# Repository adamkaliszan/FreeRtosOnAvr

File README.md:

# FreeRtosOnAvr

An alternative for arduino. Multitasking firmware provides great flexibility.

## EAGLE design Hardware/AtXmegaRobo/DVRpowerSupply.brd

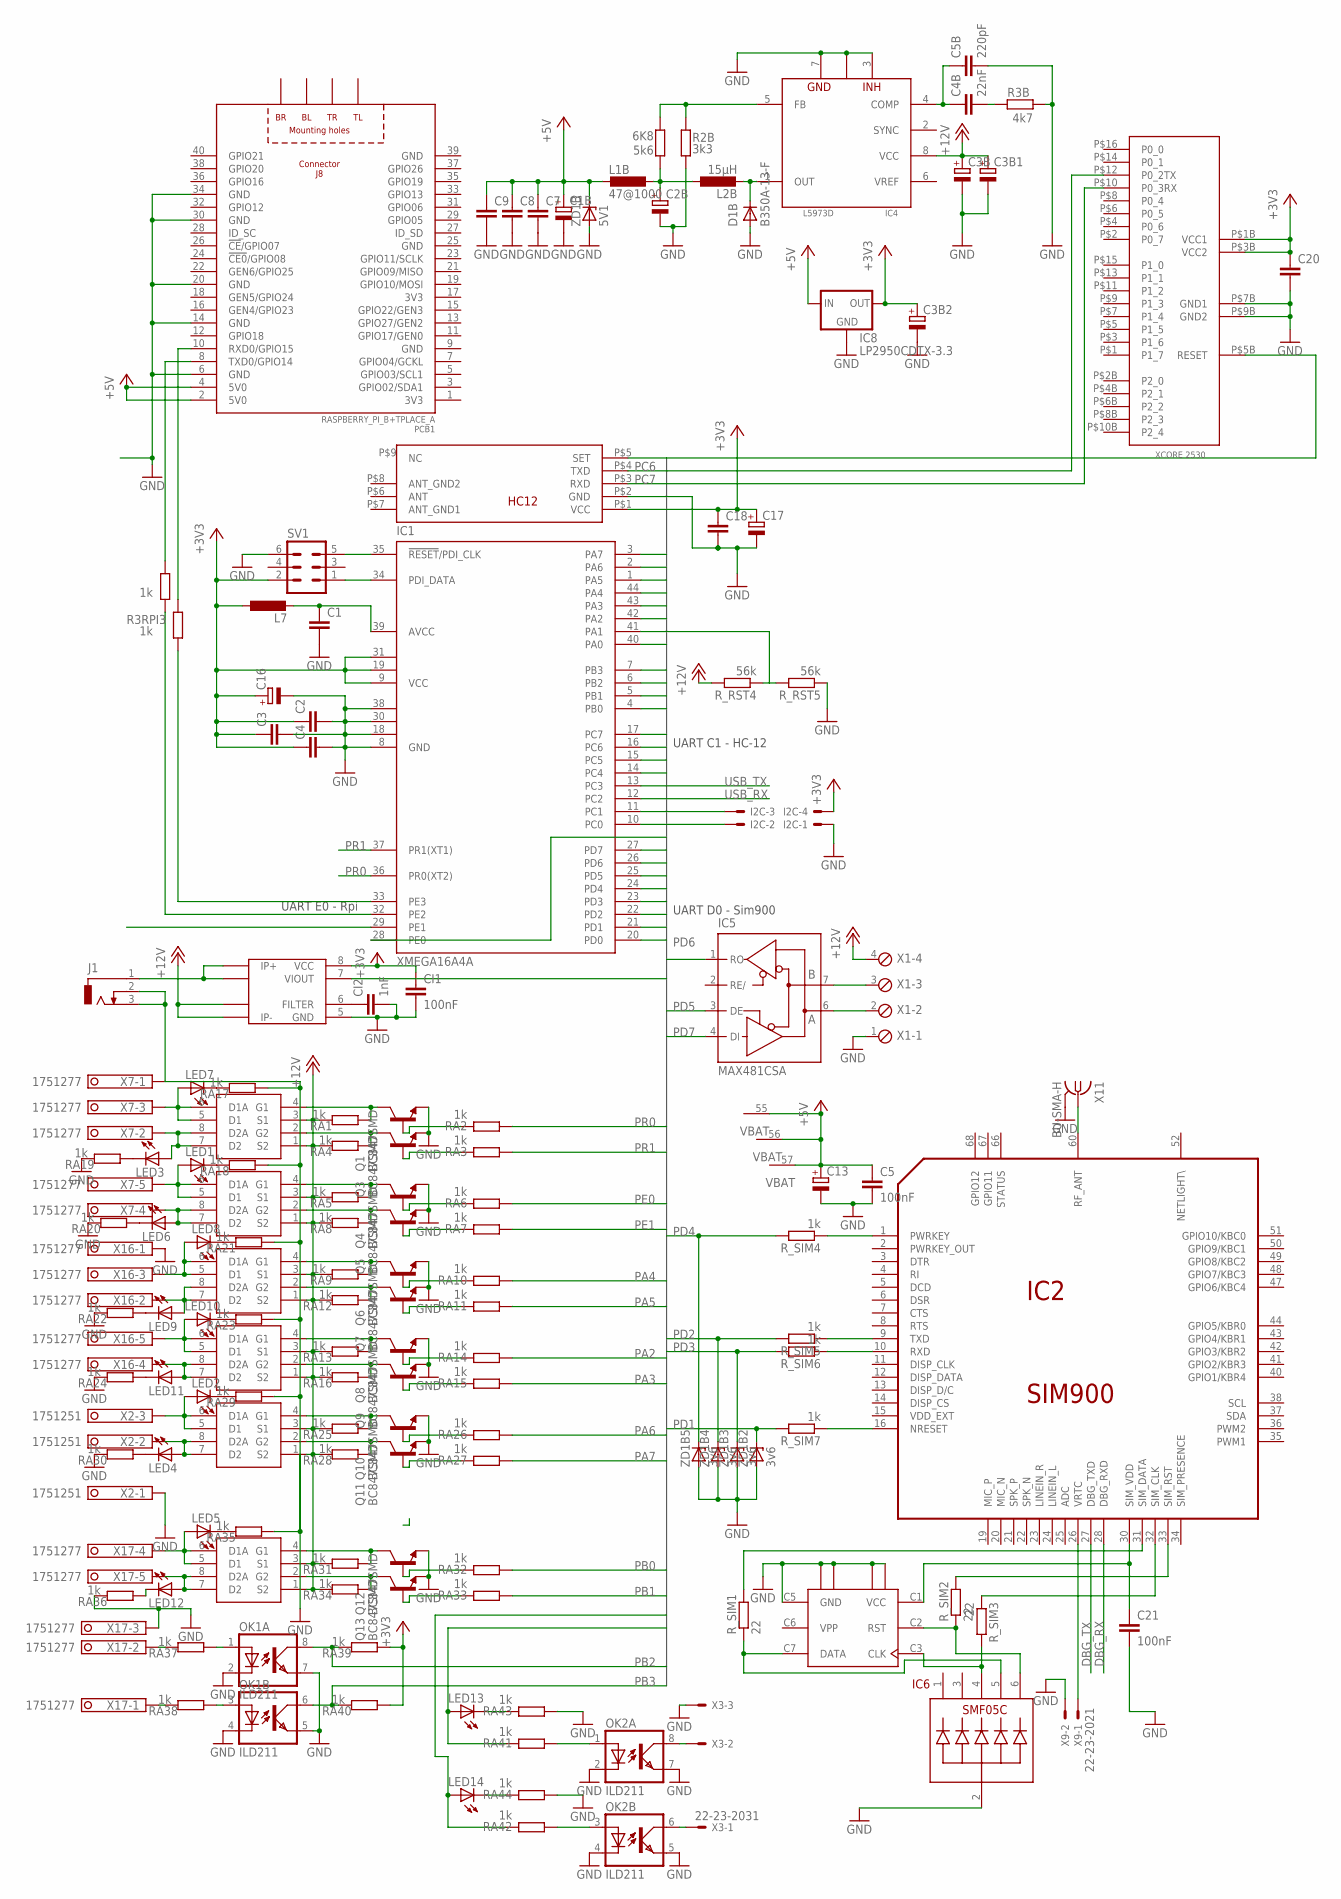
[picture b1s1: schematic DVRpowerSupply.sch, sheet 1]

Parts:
6K8: 5k6; R1206
C1, C2, C3, C4, C18, C20: C-EUC0805; C0805
C1B, C2B, C3B, C16: CPOL-EU153CLV-0405; 153CLV-0405
C3B1, C13: CPOL-EU153CLV-0605; 153CLV-0605
C3B2: CPOL-EU150CLZ-0810; 150CLZ-0810
C4B: 22nF; C0805
C5, C21: 100nF; C1206
C5B: 220pF; C0805
C7, C8, C9: C-EUC1206K; C1206K
C17: CPOL-EU140CLH-0810; 140CLH-0810
CI1: 100nF; C0805
CI2: 1nF; C0805
D1B: B350A-13-F; SMA-DO214AC
I2C: 22-23-2041
IC1: XMEGA16A4A; TQFP44
IC2: SIM900
IC4: L5973D; HSOP8-PAD
IC5: MAX481CSA; SO08
IC6: SMF05C; SC-70-6
IC8: LP2950CDTX-3.3; DPACK
J1: DCJ0303
L1B: 47@1000; L4532P
L2B: 15µH; POWER-CHOKE_WE-TPC
L7: L-EUL4035M; L4035M
LED1, LED2, LED3, LED4, LED5, LED6, LED7, LED8, LED9, LED10, LED11, LED12, LED13, LED14: LEDCHIPLED_0805; CHIPLED_0805
OK1, OK2: ILD211; SOIC08
PCB1: RASPBERRY_PI_B+TPLACE_A; RASPBERRY_PI_APLUS_TPLACE
Q1, Q3, Q4, Q5, Q6, Q7, Q8, Q9, Q10, Q11, Q12, Q13: BC847SMD; SOT23
R2B: 3k3; R1206
R3B: 4k7; R1206
R3RPI2, R3RPI3: 1k; R1206
RA1, RA2, RA3, RA4, RA5, RA6, RA7, RA8, RA9, RA10, RA11, RA12, RA13, RA14, RA15, RA16, RA17, RA18, RA19, RA20, RA21, RA22, RA23, RA24, RA25, RA26, RA27, RA28, RA29, RA30, RA31, RA32, RA33, RA34, RA35, RA36, RA37, RA38, RA39, RA40, RA41, RA42, RA43, RA44: 1k; R0805
R_RST4, R_RST5: 56k; R1206
R_SIM1, R_SIM2, R_SIM3: 22; R1206
R_SIM4, R_SIM5, R_SIM6, R_SIM7: 1k; R1206
SV1: ML6
U$1, U$2, U$9, U$10, U$11, U$12: AO4801A; SO-08
U$3: HC-12
U$4: XCORE2530
U$7: SCU-W0822XR-06115R-BCA0; 115R-BCA0
U$8: ACS712SO8; SO-08M
X1: MPT4; 4POL254
X2: 1751251
X3: 22-23-2031
X7, X16, X17: 1751277
X9: 22-23-2021
X11: BU-SMA-H
ZD1B: 5V1; SOD80C
ZD1B2, ZD1B3, ZD1B4, ZD1B5: 3v6; SOD80C

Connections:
3V3: PCB1.1 (3V3), PCB1.17 (3V3)
+3V3: C2.1, C3.1, C3B2.+, C4.1, C16.+, C17.+, C18.1, C20.1, CI1.1, I2C.4, IC1.9 (VCC), IC1.19 (VCC1), IC1.31 (VCC2), IC5.8 (VCC), IC8.3 (OUT), L7.1, RA39.1, RA40.1, SV1.2, U$3.P$1 (VCC), U$4.P$1B (VCC1), U$4.P$3B (VCC2), U$8.8 (VCC); also elsewhere on the board
+5V: C1B.+, C5.1, C7.1, C8.1, C9.1, C13.+, IC2.55 (VBAT), IC2.56 (VBAT), IC2.57 (VBAT), IC8.1 (IN), L1B.2, PCB1.2 (5V0), PCB1.4 (5V0), ZD1B.C; also elsewhere on the board
+12V: C3B.+, C3B1.+, IC4.8 (VCC), RA1.2, RA4.2, RA5.2, RA8.2, RA9.2, RA12.2, RA13.2, RA16.2, RA25.2, RA28.2, RA31.2, RA34.2, R_RST4.2, U$1.1 (S2), U$1.3 (S1), U$2.1 (S2), U$2.3 (S1), U$8.3 (IP-3), U$8.4 (IP-), U$9.1 (S2), U$9.3 (S1), U$10.1 (S2), U$10.3 (S1), U$11.1 (S2), U$11.3 (S1), U$12.1 (S2), U$12.3 (S1), X1.4
AVCC: C1.1, IC1.39 (AVCC), L7.2
COMP2: C4B.1, C5B.1, IC4.4 (COMP)
CPU_RST: IC1.35 (!RESET!/PDI_CLK), SV1.5
DBG_RX: IC2.28 (DBG_RXD); also elsewhere on the board
DBG_TX: IC2.27 (DBG_TXD); also elsewhere on the board
GND: C1.2, C1B.-, C2.2, C2B.-, C3.2, C3B.-, C3B1.-, C3B2.-, C4.2, C5.2, C5B.2, C7.2, C8.2, C9.2, C13.-, C16.-, C17.-, C18.2, C20.2, C21.2, CI1.2, CI2.2, D1B.A, I2C.1, IC1.8 (GND), IC1.18 (GND1), IC1.30 (GND2), IC1.38 (GND3), IC2.17 (GND), IC2.18 (GND), IC2.29 (GND), IC2.39 (GND), IC2.45 (GND), IC2.46 (GND), IC2.53 (GND), IC2.54 (GND), IC2.58 (GND), IC2.59 (GND), IC2.61 (GND), IC2.62 (GND), IC2.63 (GND), IC2.64 (GND), IC2.65 (GND), IC4.3 (INH), IC4.7 (GND), IC4.P (GND), IC5.5 (GND), IC6.2, IC8.4 (GND), J1.2, J1.3, OK1.2 (C), OK1.4 (C), OK1.5 (EMIT), OK1.7 (EMIT), OK2.2 (C), OK2.4 (C), OK2.5 (EMIT), OK2.7 (EMIT), PCB1.6 (GND), PCB1.9 (GND), PCB1.14 (GND), PCB1.20 (GND), PCB1.25 (GND), PCB1.30 (GND), PCB1.34 (GND), PCB1.39 (GND), Q1.2 (E), Q3.2 (E), Q4.2 (E), Q5.2 (E), Q6.2 (E), Q7.2 (E), Q8.2 (E), Q9.2 (E), Q10.2 (E), Q11.2 (E), Q12.2 (E), Q13.2 (E), R2B.1, R3B.1, RA17.1, RA18.1, RA19.2, RA20.2, RA21.1, RA22.2, RA23.1, RA24.2, RA29.1, RA30.2, RA35.1, RA36.2, RA43.1, RA44.1, R_RST5.1, SV1.6, U$3.P$2 (GND), U$4.P$7B (GND1), U$4.P$9B (GND2), U$7.C5 (GND), U$7.P$1 (GND4), U$7.P$2 (GND3), U$7.P$3 (GND2), U$7.P$4 (GND1), U$8.5 (GND), X1.1, X2.1, X3.3, X7.1, X9.2, X11.2, X11.3 (2), X11.4 (2), X11.5 (2), X16.1, X17.3, ZD1B.A, ZD1B2.A, ZD1B3.A, ZD1B4.A, ZD1B5.A; also elsewhere on the board
IC4_FB: 6K8.1, IC4.5 (FB), R2B.2
unnamed: OK2.6 (COL), X3.1
unnamed: OK2.8 (COL), X3.2
unnamed: PCB1.8 (TXD0/GPIO14), R3RPI2.2
unnamed: LED4.A, U$11.7 (D2), U$11.8 (D2A), X2.2
unnamed: LED7.A, U$1.5 (D1), U$1.6 (D1A), X7.3
unnamed: LED3.A, U$1.7 (D2), U$1.8 (D2A), X7.2
unnamed: LED7.C, RA17.2
unnamed: LED1.A, U$2.5 (D1), U$2.6 (D1A), X7.5
unnamed: LED2.A, U$11.5 (D1), U$11.6 (D1A), X2.3
unnamed: Q10.3 (C), RA25.1, U$11.4 (G1)
unnamed: CI2.1, U$8.6 (FILTER)
unnamed: LED6.A, U$2.7 (D2), U$2.8 (D2A), X7.4
unnamed: LED8.A, U$9.5 (D1), U$9.6 (D1A), X16.3
unnamed: LED9.A, U$9.7 (D2), U$9.8 (D2A), X16.2
unnamed: LED11.A, U$10.7 (D2), U$10.8 (D2A), X16.4
unnamed: D1B.K (C), IC4.1 (OUT), L2B.2
unnamed: 6K8.2, C2B.+, L1B.1, L2B.1
unnamed: LED10.A, U$10.5 (D1), U$10.6 (D1A), X16.5
unnamed: OK2.1 (A), RA41.1
unnamed: Q1.3 (C), RA1.1, U$1.4 (G1)
unnamed: C4B.2, R3B.2
unnamed: IC2.9 (TXD), R_SIM5.1
unnamed: Q4.3 (C), RA5.1, U$2.4 (G1)
unnamed: Q1.1 (B), RA2.2
unnamed: Q3.1 (B), RA3.2
unnamed: IC2.26 (VRTC), X9.1
unnamed: Q3.3 (C), RA4.1, U$1.2 (G2)
unnamed: IC2.10 (RXD), R_SIM6.1
unnamed: OK2.3 (A), RA42.1
unnamed: Q10.1 (B), RA26.2
unnamed: IC2.16 (NRESET), R_SIM7.1
unnamed: PCB1.10 (RXD0/GPIO15), R3RPI3.2
unnamed: IC2.60 (RF_ANT), X11.1
unnamed: Q4.1 (B), RA6.2
unnamed: Q5.1 (B), RA7.2
unnamed: Q5.3 (C), RA8.1, U$2.2 (G2)
unnamed: Q6.3 (C), RA9.1, U$9.4 (G1)
unnamed: Q6.1 (B), RA10.2
unnamed: Q7.1 (B), RA11.2
unnamed: Q7.3 (C), RA12.1, U$9.2 (G2)
unnamed: Q8.3 (C), RA13.1, U$10.4 (G1)
unnamed: Q8.1 (B), RA14.2
unnamed: Q9.1 (B), RA15.2
unnamed: Q9.3 (C), RA16.1, U$10.2 (G2)
unnamed: LED1.C, RA18.2
unnamed: LED3.C, RA19.1
unnamed: LED6.C, RA20.1
unnamed: LED8.C, RA21.2
unnamed: LED9.C, RA22.1
unnamed: LED10.C, RA23.2
unnamed: LED11.C, RA24.1
unnamed: Q11.1 (B), RA27.2
unnamed: Q11.3 (C), RA28.1, U$11.2 (G2)
unnamed: LED2.C, RA29.2
unnamed: LED4.C, RA30.1
unnamed: LED12.A, U$12.7 (D2), U$12.8 (D2A), X17.5
unnamed: LED5.A, U$12.5 (D1), U$12.6 (D1A), X17.4
unnamed: Q12.3 (C), RA31.1, U$12.4 (G1)
unnamed: Q12.1 (B), RA32.2
unnamed: Q13.1 (B), RA33.2
unnamed: Q13.3 (C), RA34.1, U$12.2 (G2)
unnamed: LED5.C, RA35.2
unnamed: LED12.C, RA36.1
unnamed: RA37.2, X17.2
unnamed: OK1.1 (A), RA37.1
unnamed: RA38.2, X17.1
unnamed: OK1.3 (A), RA38.1
unnamed: LED13.C, RA43.2
unnamed: LED14.C, RA44.2
PA0: IC1.40 (PA0), U$8.7 (VIOUT)
PA1: IC1.41 (PA1), R_RST4.1, R_RST5.2
PA2: IC1.42 (PA2), RA14.1
PA3: IC1.43 (PA3), RA15.1
PA4: IC1.44 (PA4), RA10.1
PA5: IC1.1 (PA5), RA11.1
PA6: IC1.2 (PA6), RA26.1
PA7: IC1.3 (PA7), RA27.1
PB0: IC1.4 (PB0), RA32.1
PB1: IC1.5 (PB1), RA33.1
PB2: IC1.6 (PB2), OK1.8 (COL), RA39.2
PB3: IC1.7 (PB3), OK1.6 (COL), RA40.2
PC0: I2C.2, IC1.10 (PC0)
PC1: I2C.3, IC1.11 (PC1)
PC4: IC1.14 (PC4), LED14.A, RA42.2
PC5: IC1.15 (PC5), LED13.A, RA41.2
PC6: IC1.16 (PC6), U$3.P$4 (TXD), U$4.P$12 (P0_2TX)
PC7: IC1.17 (PC7), U$3.P$3 (RXD), U$4.P$10 (P0_3RX)
PD0: IC1.20 (PD0), U$3.P$5 (SET), U$4.P$5B (RESET)
PD1: IC1.21 (PD1), R_SIM7.2, ZD1B2.C
PD2: IC1.22 (PD2), R_SIM5.2, ZD1B4.C
PD3: IC1.23 (PD3), R_SIM6.2, ZD1B3.C
PD4: IC1.24 (PD4), R_SIM4.2, ZD1B5.C
PD5: IC1.25 (PD5), IC5.3 (DE)
PD6: IC1.26 (PD6), IC5.1 (RO)
PD7: IC1.27 (PD7), IC5.4 (DI)
PDI_DTA: IC1.34 (PDI_DATA), SV1.1
PE0: IC1.28 (PE0), RA6.1
PE1: IC1.29 (PE1), RA7.1
PE2: IC1.32 (PE2), R3RPI2.1
PE3: IC1.33 (PE3), R3RPI3.1
PR0: IC1.36 (PR0(XT2)), RA2.1
PR1: IC1.37 (PR1(XT1)), RA3.1
PWR: J1.1, U$8.1 (IP+), U$8.2 (IP+2)
RS_485_A: IC5.6 (A), X1.2
RS_485_B: IC5.7 (B), X1.3
SIM900PWRKEY: IC2.1 (PWRKEY), R_SIM4.1
SIMCLS_S: IC6.4, R_SIM3.2, U$7.C3 (CLK)
SIMRSTS: IC6.6, R_SIM2.1, U$7.C2 (RST)
SIM_CLK: IC2.32 (SIM_CLK), R_SIM3.1
SIM_DTA: IC2.31 (SIM_DATA), R_SIM1.2
SIM_DTA_S: IC6.5, R_SIM1.1, U$7.C7 (DATA)
SIM_RST: IC2.33 (SIM_RST), R_SIM2.2
SIM_VCC: C21.1, IC2.30 (SIM_VDD), U$7.C1 (VCC)
USB_RX: IC1.12 (PC2); also elsewhere on the board
USB_TX: IC1.13 (PC3); also elsewhere on the board
VPP: U$7.C6 (VPP)

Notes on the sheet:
UART C1 - HC-12
UART D0 - Sim900
UART E0 - Rpi

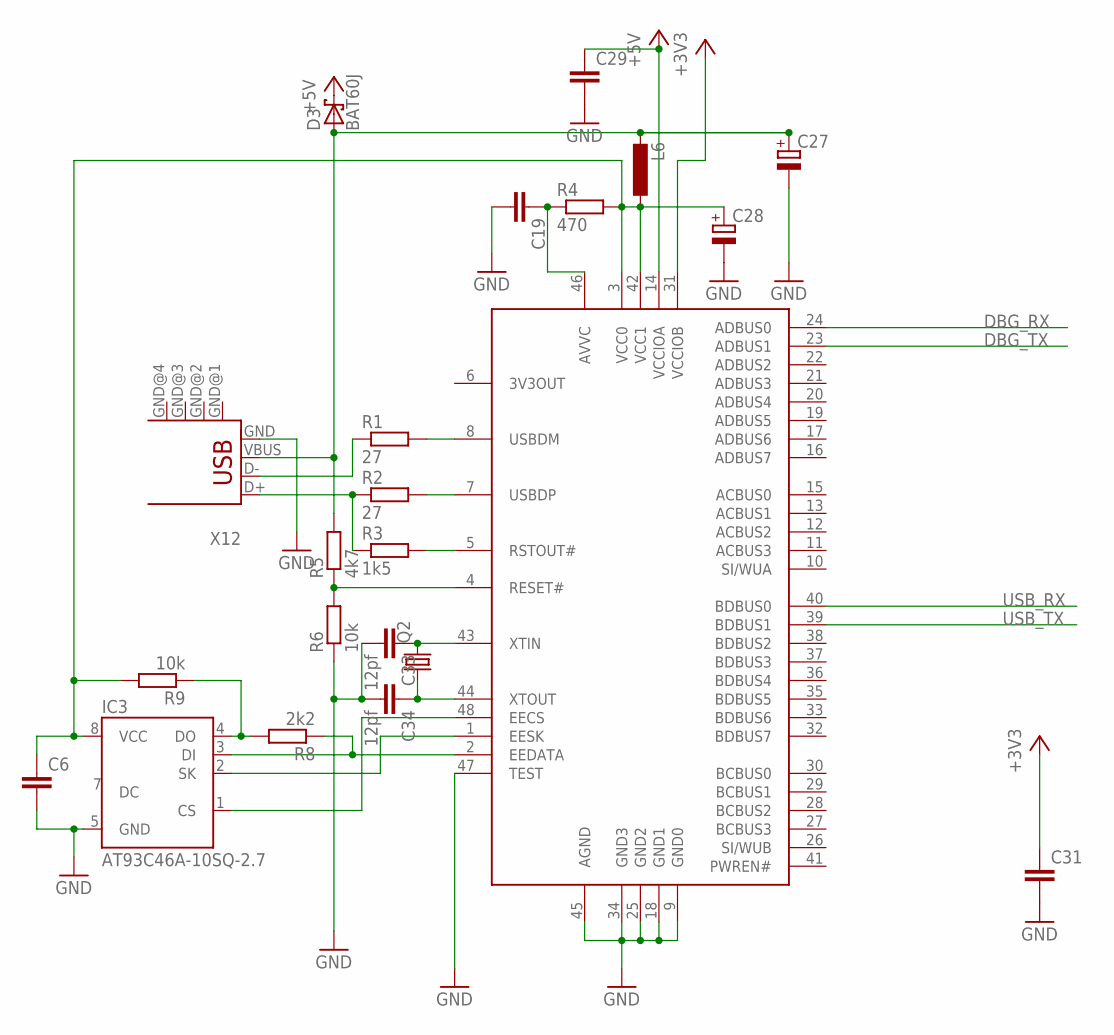
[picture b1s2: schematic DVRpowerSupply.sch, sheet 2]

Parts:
C6: C-EUC0805K; C0805K
C19: C-EUC0805; C0805
C27, C28: CPOL-EU153CLV-0405; 153CLV-0405
C29, C31: C-EUC1206; C1206
C33, C34: 12pf; C0805
D3: BAT60J; SOD323_ST
IC3: AT93C46A-10SQ-2.7; SOIC8
IC7: FT2232C; LQFP
L6: L-EUL2012C; L2012C
Q2: CRYSTALHC49S; HC49/S
R1, R2: 27; M1206
R3: 1k5; M1206
R4: 470; M0805
R5: 4k7; M1206
R6, R9: 10k; M1206
R8: 2k2; M1206
X12: USB-SHIELD; USB-M-S1

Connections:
+3V3: C31.1, IC7.31 (VCCIOB); also elsewhere on the board
+5V: C29.1, D3.C, IC7.14 (VCCIOA); also elsewhere on the board
DBG_RX: IC7.24 (ADBUS0); also elsewhere on the board
DBG_TX: IC7.23 (ADBUS1); also elsewhere on the board
FD_DI: IC3.3 (DI), IC7.2 (EEDATA), R8.1
FT_AVCC: C19.1, IC7.46 (AVVC), R4.1
FT_CS: IC3.1 (CS), IC7.48 (EECS)
FT_DO: IC3.4 (DO), R8.2, R9.1
FT_SK: IC3.2 (SK), IC7.1 (EESK)
FT_VCC: C6.1, C28.+, IC3.8 (VCC), IC7.3 (VCC0), IC7.42 (VCC1), L6.1, R4.2, R9.2
GND: C6.2, C19.2, C27.-, C28.-, C29.2, C31.2, C33.2, C34.2, IC3.5 (GND), IC7.9 (GND0), IC7.18 (GND1), IC7.25 (GND2), IC7.34 (GND3), IC7.45 (AGND), IC7.47 (TEST), R6.1, X12.GND; also elsewhere on the board
unnamed: IC7.8 (USBDM), R1.2
unnamed: IC7.7 (USBDP), R2.2
unnamed: R2.1, R3.1, X12.D+
unnamed: R1.1, X12.D-
unnamed: IC7.5 (RSTOUT#), R3.2
unnamed: C33.1, IC7.43 (XTIN), Q2.2
unnamed: C34.1, IC7.44 (XTOUT), Q2.1
unnamed: IC7.4 (RESET#), R5.1, R6.2
USB_RX: IC7.40 (BDBUS0); also elsewhere on the board
USB_TX: IC7.39 (BDBUS1); also elsewhere on the board
V_USB: C27.+, D3.A, L6.2, R5.2, X12.VBUS

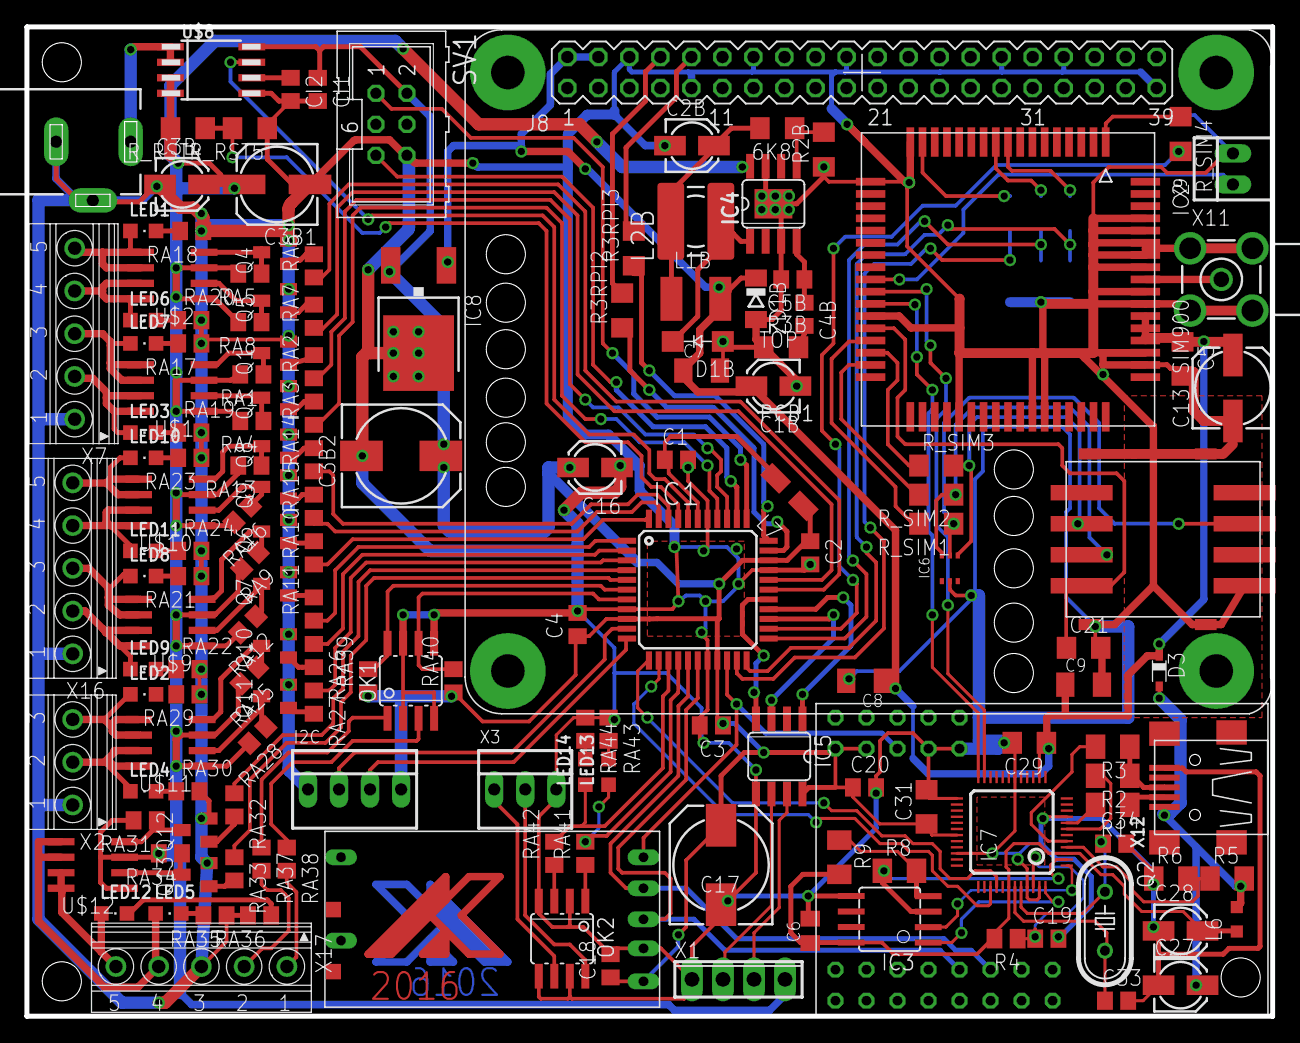
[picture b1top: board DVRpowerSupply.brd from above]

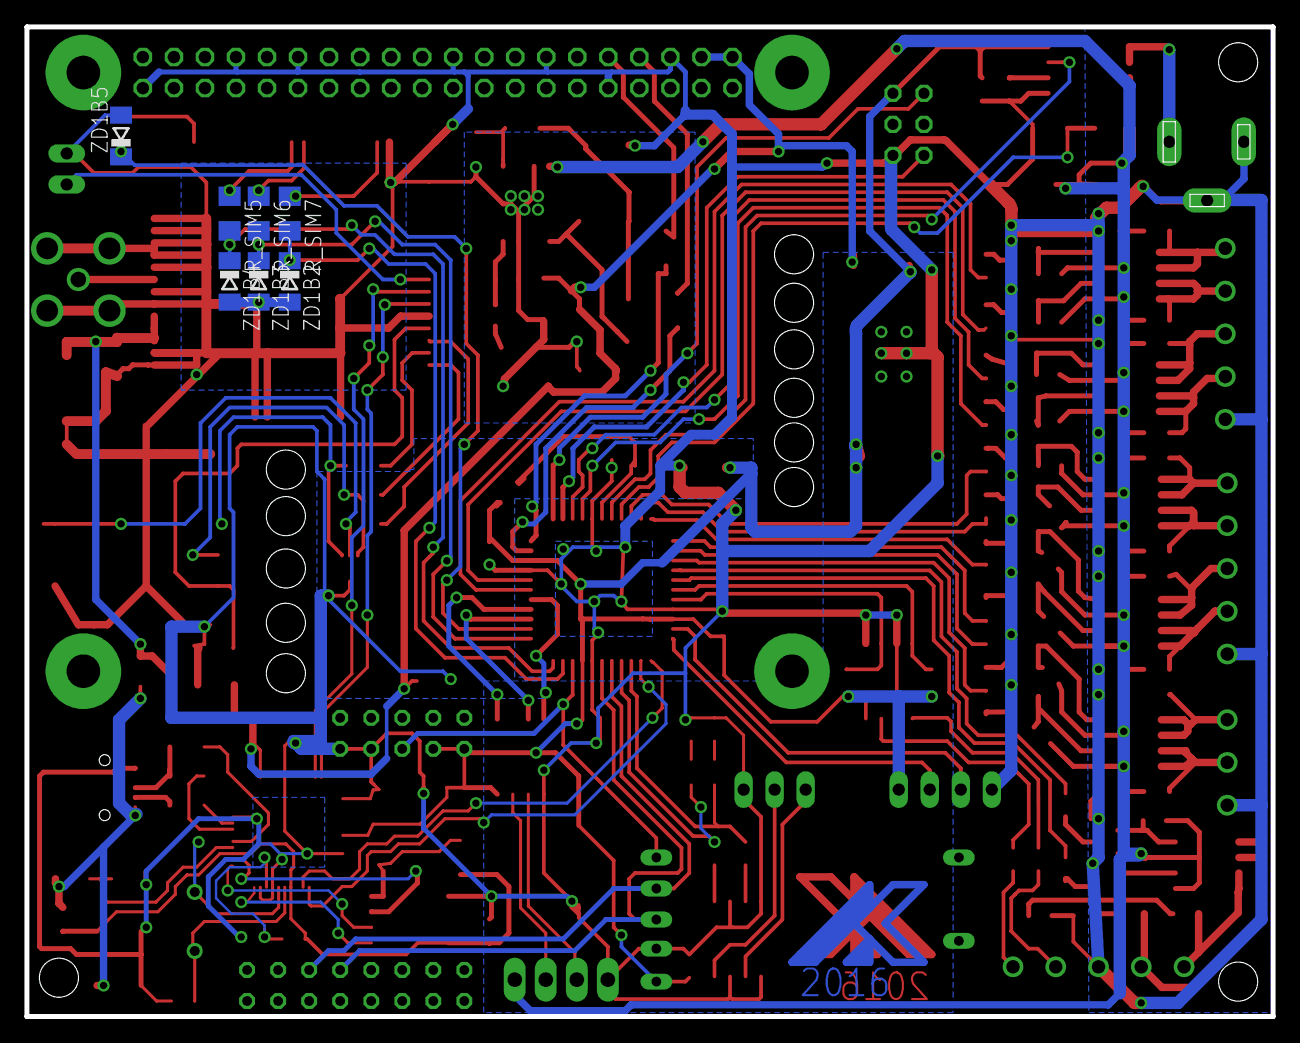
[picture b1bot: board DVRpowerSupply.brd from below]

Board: 2 copper layers, 102.0 x 81.0 mm, 170 parts (8 on the bottom side), 141 nets.

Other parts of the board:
U$5, U$6: LOGO

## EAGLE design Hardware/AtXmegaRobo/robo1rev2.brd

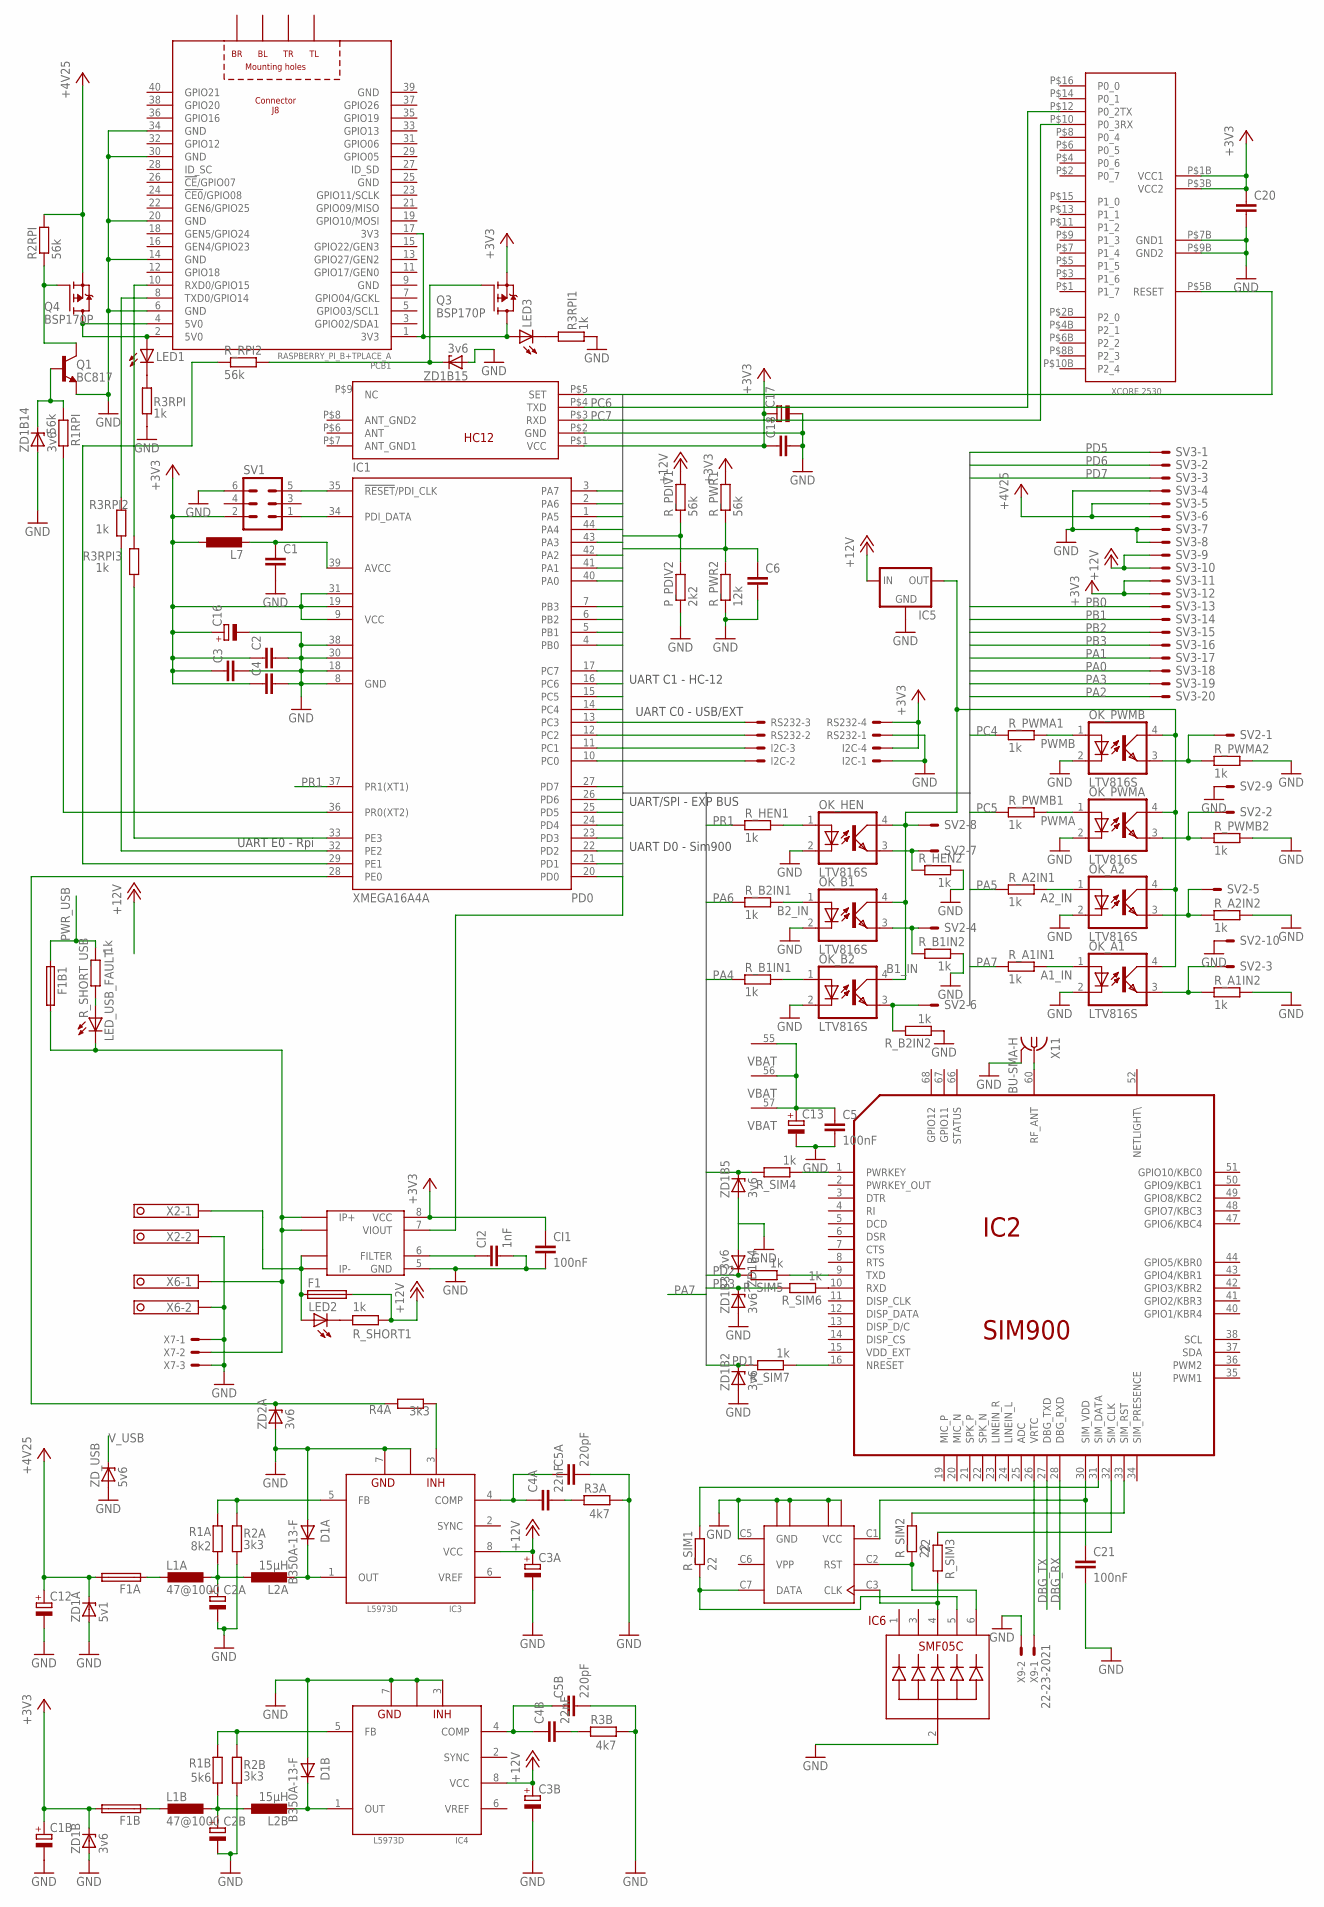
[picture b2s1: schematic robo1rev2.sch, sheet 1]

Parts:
C1, C2, C3, C4, C6, C18, C20: C-EUC0805; C0805
C1B, C2A, C2B, C3A, C3B, C16: CPOL-EU153CLV-0405; 153CLV-0405
C4A, C4B: 22nF; C0805
C5, C21: 100nF; C1206
C5A, C5B: 220pF; C0805
C12, C17: CPOL-EU140CLH-0810; 140CLH-0810
C13: CPOL-EU153CLV-0605; 153CLV-0605
CI1: 100nF; C0805
CI2: 1nF; C0805
D1A, D1B: B350A-13-F; SMA-DO214AC
F1, F1A, F1B: PICOFUSE1812; C1812K
F1B1: PICOFUSE1206; C1206K
I2C: 22-23-2041
IC1: XMEGA16A4A; TQFP44
IC2: SIM900
IC3, IC4: L5973D; HSOP8-PAD
IC5: 78LXX
IC6: SMF05C; SC-70-6
L1A: 47@1000; L4532M
L1B: 47@1000; L4532P
L2A, L2B: 15µH; POWER-CHOKE_WE-TPC
L7: L-EUL4035M; L4035M
LED1, LED2, LED3: LS_T679-D2E2-1; PLCC2
LED_USB_FAULT: LS_T679-D2E2-1; PLCC2
OK_A1, OK_A2: LTV816S; SMD4
OK_B1, OK_B2: LTV816S; SMD4
OK_HEN: LTV816S; SMD4
OK_PWMA: LTV816S; SMD4
OK_PWMB: LTV816S; SMD4
PCB1: RASPBERRY_PI_B+TPLACE_A; RASPBERRY_PI_APLUS_TPLACE
P_PDIV2: 2k2; R1206
Q1: BC817; SOT23-BEC
Q3, Q4: BSP170P; SOT223
R1A: 8k2; R1206
R1B: 5k6; R1206
R1RPI, R2RPI: 56k; R1206
R2A, R2B: 3k3; R1206
R3A: 4k7; R0805
R3B: 4k7; R1206
R3RPI, R3RPI1, R3RPI2, R3RPI3: 1k; R1206
R4A: 3k3; R0805
RS232: 22-23-2041
R_A1IN1, R_A1IN2, R_A2IN1, R_A2IN2: 1k; R0805
R_B1IN1, R_B1IN2, R_B2IN1, R_B2IN2: 1k; R0805
R_HEN1, R_HEN2: 1k; R0805
R_PDIV1: 56k; R1206
R_PWMA1, R_PWMA2: 1k; R0805
R_PWMB1, R_PWMB2: 1k; R0805
R_PWR1: 56k; R0805
R_PWR2: 12k; R0805
R_RPI2: 56k; R1206
R_SHORT1: 1k; R1206
R_SHORT_USB: 1k; R1206
R_SIM1, R_SIM2, R_SIM3: 22; R1206
R_SIM4, R_SIM5, R_SIM6, R_SIM7: 1k; R1206
SV1: ML6
SV2: ML10E; ML10
SV3: ML20E; ML20
U$3: HC-12
U$4: XCORE2530
U$7: SCU-W0822XR-06115R-BCA0; 115R-BCA0
U$8: ACS712SO8; SO-08M
X2, X6: 1751248
X7: 22-23-2031
X9: 22-23-2021
X11: BU-SMA-H
ZD1A: 5v1; SOD80C
ZD1B, ZD1B2, ZD1B3, ZD1B4, ZD1B5, ZD1B14, ZD1B15, ZD2A: 3v6; SOD80C
ZD_USB: 5v6; SOD80C

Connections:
+3V3: C1B.+, C2.1, C3.1, C4.1, C16.+, C17.+, C18.1, C20.1, CI1.1, F1B.2, I2C.4, IC1.9 (VCC), IC1.19 (VCC1), IC1.31 (VCC2), L7.1, Q3.3 (S), RS232.4, R_PWR1.2, SV1.2, SV3.11, SV3.12, U$3.P$1 (VCC), U$4.P$1B (VCC1), U$4.P$3B (VCC2), U$8.8 (VCC), ZD1B.C; also elsewhere on the board
+4V4_BF: C2A.+, L1A.1, L2A.1, R1A.2
+4V35: C5.1, C12.+, C13.+, F1A.2, IC2.55 (VBAT), IC2.56 (VBAT), IC2.57 (VBAT), Q4.3 (S), R2RPI.2, SV3.5, SV3.6, ZD1A.C; also elsewhere on the board
+12V: C3A.+, C3B.+, F1.2, IC3.8 (VCC), IC4.8 (VCC), IC5.IN, R_PDIV1.2, R_SHORT1.2, SV3.9, SV3.10
A1_IN: OK_A1.1 (A), R_A1IN1.1
A2_IN: OK_A2.1 (A), R_A2IN1.1
AVCC: C1.1, IC1.39 (AVCC), L7.2
B1_IN: OK_B2.1 (A), R_B1IN1.2
B2_IN: OK_B1.1 (A), R_B2IN1.2
COMP1: C4A.1, C5A.1, IC3.4 (COMP)
COMP2: C4B.1, C5B.1, IC4.4 (COMP)
CPU_RST: IC1.35 (!RESET!/PDI_CLK), SV1.5
DBG_RX: IC2.28 (DBG_RXD); also elsewhere on the board
DBG_TX: IC2.27 (DBG_TXD); also elsewhere on the board
EXT_RX: IC1.12 (PC2), RS232.2; also elsewhere on the board
EXT_TX: IC1.13 (PC3), RS232.3; also elsewhere on the board
GND: C1.2, C1B.-, C2.2, C2A.-, C2B.-, C3.2, C3A.-, C3B.-, C4.2, C5.2, C5A.2, C5B.2, C6.2, C12.-, C13.-, C16.-, C17.-, C18.2, C20.2, C21.2, CI1.2, CI2.2, D1A.A, D1B.A, I2C.1, IC1.8 (GND), IC1.18 (GND1), IC1.30 (GND2), IC1.38 (GND3), IC2.17 (GND), IC2.18 (GND), IC2.29 (GND), IC2.39 (GND), IC2.45 (GND), IC2.46 (GND), IC2.53 (GND), IC2.54 (GND), IC2.58 (GND), IC2.59 (GND), IC2.61 (GND), IC2.62 (GND), IC2.63 (GND), IC2.64 (GND), IC2.65 (GND), IC3.7 (GND), IC3.P (GND), IC4.3 (INH), IC4.7 (GND), IC4.P (GND), IC5.GND, IC6.2, OK_A1.2 (C), OK_A2.2 (C), OK_B1.2 (C), OK_B2.2 (C), OK_HEN.2 (C), OK_PWMA.2 (C), OK_PWMB.2 (C), PCB1.6 (GND), PCB1.9 (GND), PCB1.14 (GND), PCB1.20 (GND), PCB1.25 (GND), PCB1.30 (GND), PCB1.34 (GND), PCB1.39 (GND), P_PDIV2.1, Q1.E, R2A.1, R2B.1, R3A.1, R3B.1, R3RPI.1, R3RPI1.1, RS232.1, R_A1IN2.1, R_A2IN2.1, R_B1IN2.2, R_B2IN2.1, R_HEN2.2, R_PWMA2.2, R_PWMB2.1, R_PWR2.1, SV1.6, SV2.9, SV2.10, SV3.4, SV3.7, SV3.8, U$3.P$2 (GND), U$4.P$7B (GND1), U$4.P$9B (GND2), U$7.C5 (GND), U$7.P$1 (GND4), U$7.P$2 (GND3), U$7.P$3 (GND2), U$7.P$4 (GND1), U$8.5 (GND), X2.2, X6.2, X7.1, X7.3, X9.2, X11.2, X11.3 (2), X11.4 (2), X11.5 (2), ZD1A.A, ZD1B.A, ZD1B2.A, ZD1B3.A, ZD1B4.A, ZD1B5.A, ZD1B14.A, ZD1B15.A, ZD2A.A, ZD_USB.A; also elsewhere on the board
unnamed: IC1.34 (PDI_DATA), SV1.1
unnamed: PCB1.8 (TXD0/GPIO14), R3RPI2.2
unnamed: IC3.3 (INH), R4A.1
unnamed: F1B.1, L1B.2
unnamed: F1A.1, L1A.2
unnamed: LED2.C, R_SHORT1.1
unnamed: CI2.1, U$8.6 (FILTER)
unnamed: Q1.B, R1RPI.1, ZD1B14.C
unnamed: Q1.C, Q4.1 (G), R2RPI.1
unnamed: LED1.C, R3RPI.2
unnamed: D1B.K (C), IC4.1 (OUT), L2B.2
unnamed: C2B.+, L1B.1, L2B.1, R1B.2
unnamed: IC3.5 (FB), R1A.1, R2A.2
unnamed: LED3.C, R3RPI1.2
unnamed: C4B.2, R3B.2
unnamed: IC2.9 (TXD), R_SIM5.1
unnamed: D1A.K (C), IC3.1 (OUT), L2A.2
unnamed: C4A.2, R3A.2
unnamed: IC4.5 (FB), R1B.1, R2B.2
unnamed: IC2.26 (VRTC), X9.1
unnamed: IC2.10 (RXD), R_SIM6.1
unnamed: LED_USB_FAULT.A, R_SHORT_USB.1
unnamed: IC2.16 (NRESET), R_SIM7.1
unnamed: PCB1.10 (RXD0/GPIO15), R3RPI3.2
unnamed: IC2.60 (RF_ANT), X11.1
unnamed: OK_HEN.1 (A), R_HEN1.1
unnamed: OK_HEN.3 (EMIT), R_HEN2.1, SV2.7
OPT_A1: OK_A2.3 (EMIT), R_A2IN2.2, SV2.5
OPT_A2: OK_A1.3 (EMIT), R_A1IN2.2, SV2.3
OPT_A_PWM: OK_PWMB.3 (EMIT), R_PWMA2.1, SV2.1
OPT_B1: OK_B2.3 (EMIT), R_B2IN2.2, SV2.6
OPT_B2: OK_B1.3 (EMIT), R_B1IN2.1, SV2.4
OPT_B_PWM: OK_PWMA.3 (EMIT), R_PWMB2.2, SV2.2
PA0: IC1.40 (PA0), SV3.18
PA1: IC1.41 (PA1), SV3.17
PA2: IC1.42 (PA2), SV3.20
PA3: IC1.43 (PA3), SV3.19
PA4: IC1.44 (PA4), R_B1IN1.1
PA5: IC1.1 (PA5), R_A2IN1.2
PA6: IC1.2 (PA6), R_B2IN1.1
PA7: IC1.3 (PA7), R_A1IN1.2
PB0: IC1.4 (PB0), P_PDIV2.2, R_PDIV1.1, SV3.13
PB1: IC1.5 (PB1), SV3.14, U$8.7 (VIOUT)
PB2: C6.1, IC1.6 (PB2), R_PWR1.1, R_PWR2.2, SV3.15
PB3: IC1.7 (PB3), SV3.16
PC0: I2C.2, IC1.10 (PC0)
PC1: I2C.3, IC1.11 (PC1)
PC4: IC1.14 (PC4), R_PWMA1.1
PC5: IC1.15 (PC5), R_PWMB1.2
PC6: IC1.16 (PC6), U$3.P$4 (TXD), U$4.P$12 (P0_2TX)
PC7: IC1.17 (PC7), U$3.P$3 (RXD), U$4.P$10 (P0_3RX)
PD0: IC1.20 (PD0), U$3.P$5 (SET), U$4.P$5B (RESET)
PD1: IC1.21 (PD1), R_SIM7.2, ZD1B2.C
PD2: IC1.22 (PD2), R_SIM5.2, ZD1B4.C
PD3: IC1.23 (PD3), R_SIM6.2, ZD1B3.C
PD4: IC1.24 (PD4), R_SIM4.2, ZD1B5.C
PD5: IC1.25 (PD5), SV3.1
PD6: IC1.26 (PD6), SV3.2
PD7: IC1.27 (PD7), SV3.3
PE0: IC1.28 (PE0), R4A.2, ZD2A.C
PE1: IC1.29 (PE1), R_RPI2.1
PE2: IC1.32 (PE2), R3RPI2.1
PE3: IC1.33 (PE3), R3RPI3.1
PR0: IC1.36 (PR0(XT2)), R1RPI.2
PR1: IC1.37 (PR1(XT1)), R_HEN1.2
PWMA: OK_PWMA.1 (A), R_PWMB1.1
PWMB: OK_PWMB.1 (A), R_PWMA1.2
PWR: F1B1.2, LED_USB_FAULT.C, U$8.1 (IP+), U$8.2 (IP+2), X6.1, X7.2
PWR_H: F1.1, LED2.A, U$8.3 (IP-3), U$8.4 (IP-), X2.1
PWR_USB: F1B1.1, R_SHORT_USB.2; also elsewhere on the board
RPI_3V3: LED3.A, PCB1.1 (3V3), PCB1.17 (3V3), Q3.2 (D), Q3.4 (D)
RPI_5V: LED1.A, PCB1.2 (5V0), PCB1.4 (5V0), Q4.2 (D), Q4.4 (D)
RPI_CTRL_3V3: Q3.1 (G), R_RPI2.2, ZD1B15.C
SIM900PWRKEY: IC2.1 (PWRKEY), R_SIM4.1
SIMCLS_S: IC6.4, R_SIM3.2, U$7.C3 (CLK)
SIMRSTS: IC6.6, R_SIM2.1, U$7.C2 (RST)
SIM_CLK: IC2.32 (SIM_CLK), R_SIM3.1
SIM_DTA: IC2.31 (SIM_DATA), R_SIM1.2
SIM_DTA_S: IC6.5, R_SIM1.1, U$7.C7 (DATA)
SIM_RST: IC2.33 (SIM_RST), R_SIM2.2
SIM_VCC: C21.1, IC2.30 (SIM_VDD), U$7.C1 (VCC)
VPP: U$7.C6 (VPP)
V_H_LOG: IC5.OUT, OK_A1.4 (COL), OK_A2.4 (COL), OK_B1.4 (COL), OK_B2.4 (COL), OK_HEN.4 (COL), OK_PWMA.4 (COL), OK_PWMB.4 (COL), SV2.8
V_USB: ZD_USB.C; also elsewhere on the board

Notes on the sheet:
UART C1 - HC-12
UART C0 - USB/EXT
UART/SPI - EXP BUS
UART D0 - Sim900
UART E0 - Rpi

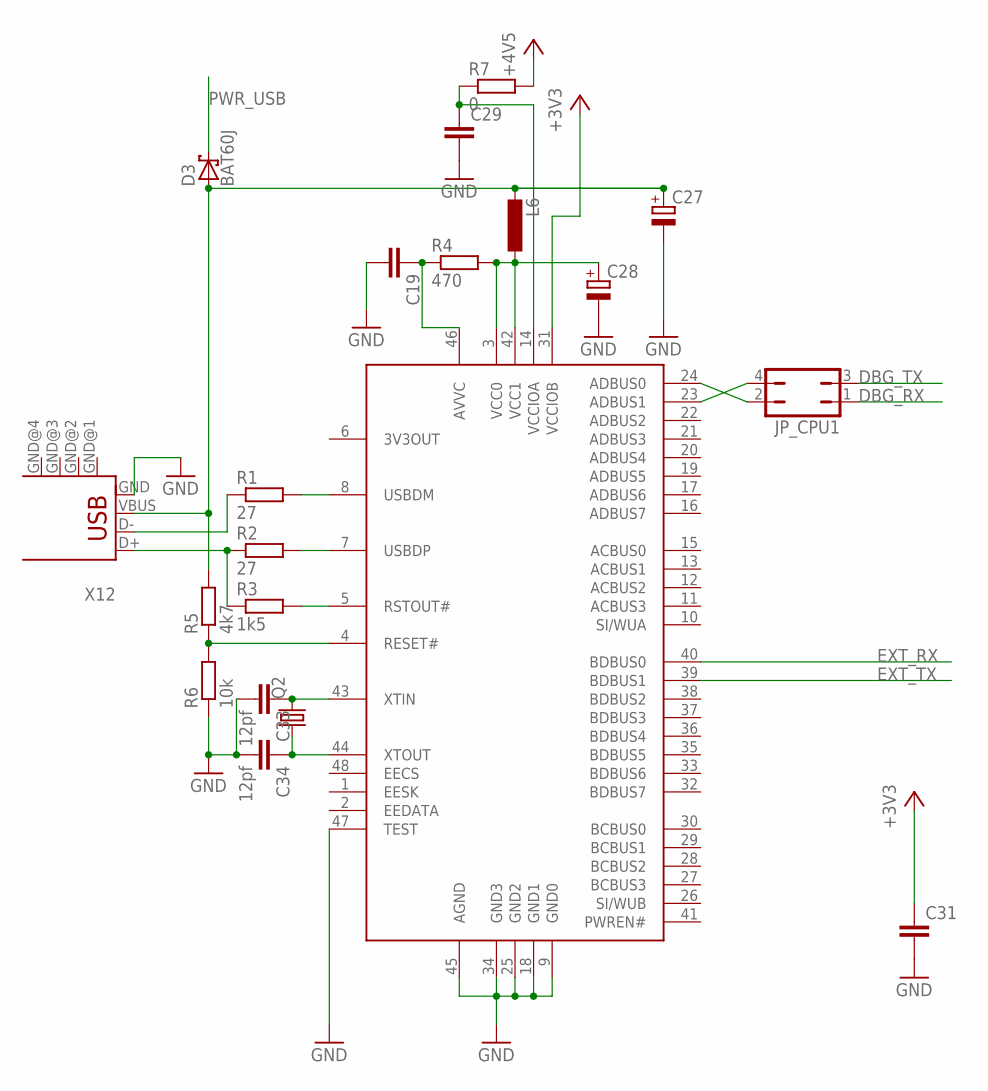
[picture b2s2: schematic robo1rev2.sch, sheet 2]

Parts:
C19: C-EUC0805; C0805
C27, C28: CPOL-EU153CLV-0405; 153CLV-0405
C29, C31: C-EUC1206; C1206
C33, C34: 12pf; C0805
D3: BAT60J; SOD323_ST
IC7: FT2232C; LQFP
JP_CPU1: JP2Q
L6: L-EUL2012C; L2012C
Q2: CRYSTALHC49S; HC49/S
R1, R2: 27; M1206
R3: 1k5; M1206
R4: 470; M0805
R5: 4k7; M1206
R6: 10k; M1206
R7: 0; M1206
X12: USB-SHIELD; USB-M-S1

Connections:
+3V3: C31.1, IC7.31 (VCCIOB); also elsewhere on the board
+4V35: R7.2; also elsewhere on the board
A_RX: IC7.23 (ADBUS1), JP_CPU1.4
A_TX: IC7.24 (ADBUS0), JP_CPU1.2
DBG_RX: JP_CPU1.1; also elsewhere on the board
DBG_TX: JP_CPU1.3; also elsewhere on the board
EXT_RX: IC7.40 (BDBUS0); also elsewhere on the board
EXT_TX: IC7.39 (BDBUS1); also elsewhere on the board
FT_AVCC: C19.1, IC7.46 (AVVC), R4.1
FT_RST: IC7.4 (RESET#), R5.1, R6.2
FT_VCC: C28.+, IC7.3 (VCC0), IC7.42 (VCC1), L6.1, R4.2
FT_XIN: C33.1, IC7.43 (XTIN), Q2.2
FT_XOUT: C34.1, IC7.44 (XTOUT), Q2.1
GND: C19.2, C27.-, C28.-, C29.2, C31.2, C33.2, C34.2, IC7.9 (GND0), IC7.18 (GND1), IC7.25 (GND2), IC7.34 (GND3), IC7.45 (AGND), IC7.47 (TEST), R6.1, X12.GND; also elsewhere on the board
unnamed: IC7.8 (USBDM), R1.2
unnamed: IC7.7 (USBDP), R2.2
unnamed: R2.1, R3.1, X12.D+
unnamed: R1.1, X12.D-
unnamed: IC7.5 (RSTOUT#), R3.2
unnamed: C29.1, IC7.14 (VCCIOA), R7.1
PWR_USB: D3.C; also elsewhere on the board
V_USB: C27.+, D3.A, L6.2, R5.2, X12.VBUS; also elsewhere on the board

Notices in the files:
parts and their libraries:
SparkFun-Sensors: Licensing: Creative Commons ShareAlike 4.0 International - https://creativecommons.org/licenses/by-sa/4.0
vreg-pulse: 2009 Draw by Ivan A-R. License CC-BY-SA 3.0
